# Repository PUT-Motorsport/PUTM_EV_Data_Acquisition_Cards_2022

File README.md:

# PUTM_EV_Data_Acquisition_Card_2022

## About the project
It's main task is to receive signals from sensors mounted on the car and analyze them and send to CAN-bus.

## Hardware design
The hardware part of the project is the PCB board which is connected to the sensors and CAN-bus. The microcontroller which is used is STM32L4P5RET6. The PCB is supply by 5VDC.

## Sensors
It receive signals from :   
 - ~~inductive sensors - there are used to measure wheels rotation speed~~
 - brake pressure sensors - which measure the pressure in the brake system
 - shutdown circuit sense:
1. BSPD
2. Overtravel switch
3. Driver's kill switch
4. Left and right kill switches
 - acceleration - from MPU on board

## Program flow diagram

)

## DMA and ADC timings consideration

The program is required to collect and relay data @ 100 ms.
Two adc peripherals are used to collect data from 3 analog sensors each.

* * *
ADC clock frequency: $32 MHz$

Sampling time: $92.5$ cycles - **reason:** High impedance inputs are used, subject to change

Oversampling: by 256

Sample conversion time: $T_{sample} + 12.5 = 105 cycles$

With oversampling: $T_{total} = 105 cycles * 256 samples = 26880 cycles$

$$
t = \frac{26800 * 3 channels}{32 * 10^6 Hz} = 2.52 * 10^{-3} s = 2.52 ms
$$

# 1D Kalman filter design for the IMU data

$$
\vec{x}(t + 1) = F(t + 1; t) * \vec{x}(t) + G * \vec{u} + w(t)
$$
$$
\vec{z} = H * \vec{x}(t)
$$

$$
\vec{x} = \begin{bmatrix} a_x \\ a_y \\ a_z \end{bmatrix}
$$

$$
F = \begin{bmatrix} 1 \\ 1 \\ 1 \end{bmatrix} \space\space\space H = \begin{bmatrix} 1 \\ 1 \\ 1 \end{bmatrix} \space\space\space G = [1] \space u = [0]
$$

$$
P(t + 1) = F(t)P(t) F(t)^T + Q(t)
$$

Since there is no way to calculate the change in acceleration, w(t) is estimated to gaussian N(0, $\sigma$) as process noise.

$$
Q(t) = \begin{bmatrix} \sigma_x \space 0 \space 0 \\ 0 \space \sigma_y \space 0 \\ 0 \space 0 \space \sigma_z\end{bmatrix}
$$

$$
\sigma_{process} = \sigma_x = \sigma_y = \sigma_z
$$

$$
R = \begin{bmatrix} ? ? ? \\ ? ? ? \\ ? ? ? \end{bmatrix}
$$

R to be selected.

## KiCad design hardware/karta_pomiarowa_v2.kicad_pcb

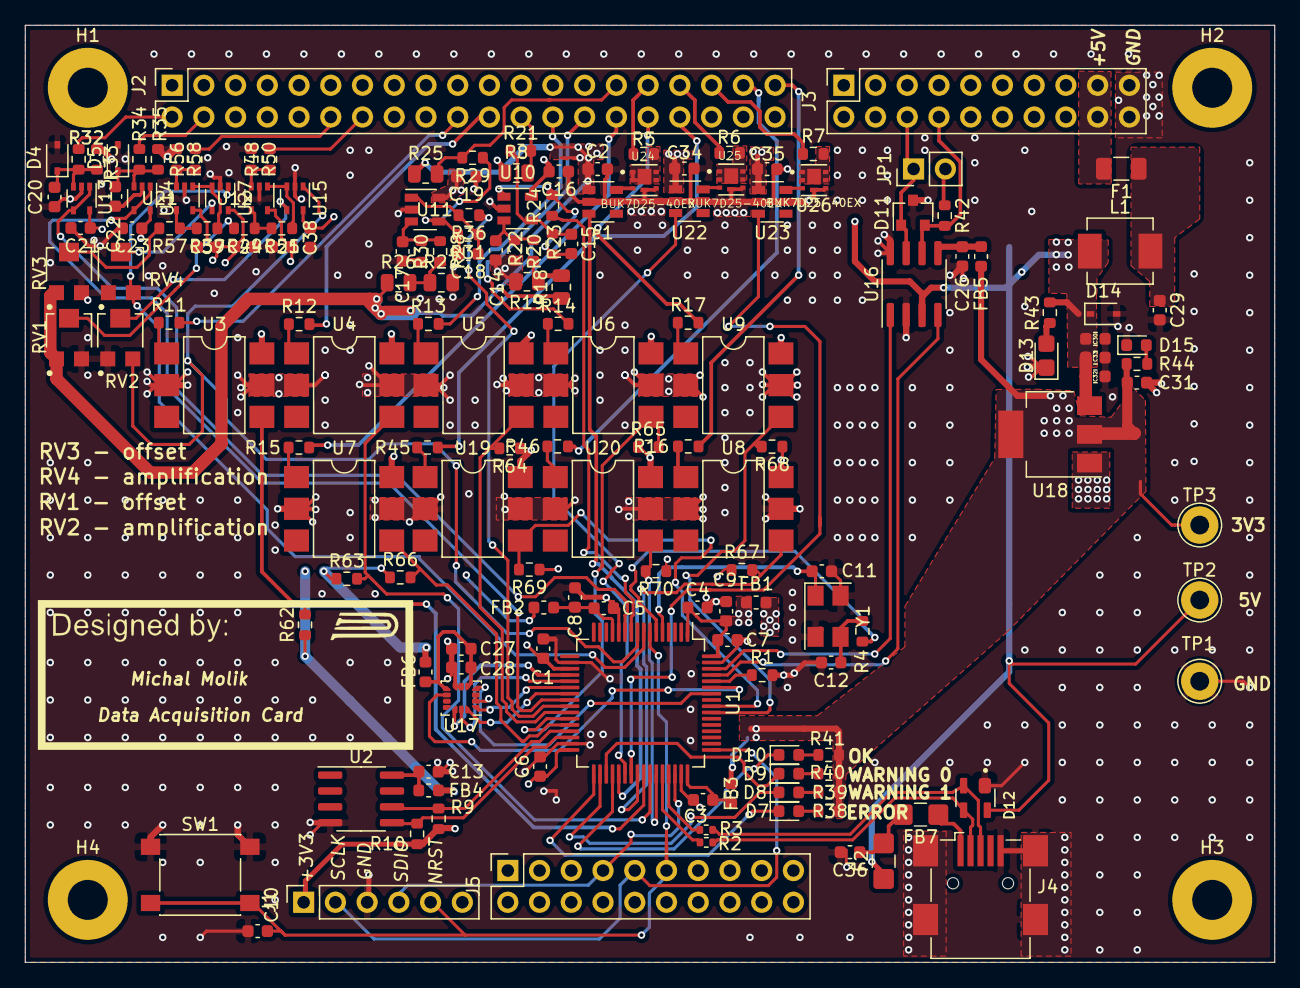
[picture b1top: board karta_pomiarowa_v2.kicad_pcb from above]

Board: 4 copper layers, 100.0 x 75.0 mm, 168 parts (0 on the bottom side), 118 nets.

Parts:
C1, C2, C3, C4, C5, C6, C7, C10, C13, C27, C28, C30, C31, C33, C34, C35, C36: 100nF; C_0603_1608Metric
C8: 1uF; C_0603_1608Metric
C9: 4.7uF; C_0603_1608Metric
C11, C12: 20p; C_0603_1608Metric
C14, C15, C17, C18: 1nF; C_0603_1608Metric
C16, C19, C20, C21, C22, C23, C24, C25, C26, C37, C38: 100n; C_0603_1608Metric
C29, C32: 10uF; C_0603_1608Metric
D4, D5: 6v5; D_SOD-323
D7, D8, D9, D10, D15: LED; LED_0603_1608Metric
D11: PESD2CAN.215; SOT-23
D12: PRTR5V0U2X; SOT190P230X110-4N
D13: LED; D_0805_2012Metric_Castellated
D14: 5.6v/6v; D_SOD-323
F1: 200mA; Fuse_1206_3216Metric
F2: 200mA; Fuse_1206_3216Metric_Castellated
FB1, FB2, FB3, FB4, FB5, FB6: 60R120MHz; L_0603_1608Metric
FB7: 1kOhm; Fuse_1206_3216Metric_Castellated
H1, H2, H3, H4: MountingHole; MountingHole_3.2mm_M3_Pad
J1: Conn_01x05_Male; PinSocket_1x06_P2.54mm_Vertical
J2: Conn_02x20_Odd_Even; PinSocket_2x20_P2.54mm_Vertical
J3, J5: Conn_02x10_Odd_Even; PinSocket_2x10_P2.54mm_Vertical
J4: USB_OTG; USB_Mini-B_Wuerth_65100516121_Horizontal
JP1: Jumper_NO_Small; PinHeader_1x02_P2.54mm_Vertical
L1: 6.8uH; L_Vishay_IHLP-2020
R1, R20, R21, R28, R29, R49, R57: 10k; R_0603_1608Metric
R2, R3: 22R; R_0402_1005Metric
R4, R42: R; R_0603_1608Metric
R5, R6, R7: 10R; R_0603_1608Metric
R8, R18, R19, R25, R26, R27: 5k; R_0805_2012Metric
R9, R10: 4.7k; R_0603_1608Metric
R11, R12, R13, R14, R15, R16, R17, R45, R46: 12k; R_0603_1608Metric
R22, R23, R30, R31, R51, R59: 47k; R_0603_1608Metric
R24, R36: 100R; R_0603_1608Metric
R32, R34, R48, R56, R62, R63, R64, R65, R66, R67, R68, R69, R70: 1k; R_0603_1608Metric
R33, R35, R38, R39, R40, R41, R44, R50, R58: 2k; R_0603_1608Metric
R43: 2.5k; R_0603_1608Metric
RV1, RV3: 2K; TRIM_TC33X-2-103E
RV2, RV4: 3K; TRIM_TC33X-2-103E
SW1: SW_MEC_5E; SW_Push_1P1T_NO_6x6mm_H9.5mm
TP1: GND; TestPoint_THTPad_D3.0mm_Drill1.5mm
TP2: 5V; TestPoint_THTPad_D3.0mm_Drill1.5mm
TP3: 3V3; TestPoint_THTPad_D3.0mm_Drill1.5mm
U1: STM32L4P5RET6; LQFP-64_10x10mm_P0.5mm
U2: M24C01-WMN; SOIC-8_3.9x4.9mm_P1.27mm
U3, U4, U5, U6, U7, U8, U9, U19, U20: H11L1; SMDIP-6_W7.62mm
U10, U11: TSX7191; SOT-23-5
U12, U13, U14, U15, U21, U27: MCP6001x-LT; SOT-353_SC-70-5
U16: ATA6561-GAQW-N; SOIC-8_3.9x4.9mm_P1.27mm
U17: IMS330DHCX; LGA-14_3x2.5mm_P0.5mm_LayoutBorder3x4y
U18: LM1117-3.3_copy; SOT-223
U22, U23: MCP14A0052T; SOT-23-6
U24, U25, U26: BUK7D25-40EX; TRANS_PMPB16EPX
Y1: 8MHz; Crystal_SMD_5032-4Pin_5.0x3.2mm
e1: MCP14A0052T; SOT-23-6

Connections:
+3V3: C16.2, C19.2, C21.2, C23.2, C24.2, C25.2, C31.1, C37.2, C38.2, FB1.1, FB2.1, FB3.1, FB4.1, FB5.1, FB6.1, J1.1, R9.1, R10.1, R38.1, R39.1, R40.1, R41.1, R44.1, R62.1, R63.1, R64.1, R65.1, R66.1, R67.1, R68.1, R69.1, R70.1, TP3.1, U3.6, U4.6, U5.6, U6.6, U7.6, U8.6, U9.6, U10.5, U11.5, U12.5, U13.5, U14.5, U15.5, U18.2, U18.4, U19.6, U20.6, U21.5, U27.5
+5V: C2.2, C30.1, C32.1, C33.1, C34.2, C35.2, D12.4, D14.1, F2.1, L1.1, R8.1, R18.1, R25.1, R26.1, R43.1, RV1.1, RV3.1, TP2.1, U16.3, U18.3, U22.1, U23.1, e1.1
+5VP: F1.2, J3.17, J3.18
/+uC: C1.1, C4.1, C6.1, C7.1, C9.1, FB1.2, U1.1, U1.19, U1.32, U1.64
/+uCa: C5.1, C8.1, FB2.2, U1.13
/+uCusb: C3.1, FB3.2, U1.48
/A0: RV4.3, U1.8, U27.1
/A1: RV2.3, U1.9, U15.1
/A2: R24.1, U1.10
/A3: U1.11, U13.1, U13.4
/A4: U1.24, U14.1, U14.4
/A5: R36.1, U1.25
/CAN_RX: U1.61, U16.4
/CAN_TRASCIVER/+3.3V_CAN: C26.1, FB5.2, U16.5
/CAN_TX: U1.62, U16.1
/DI0: R64.2, U1.26, U5.4
/DI1: R65.2, U1.27, U6.4
/DI2: R66.2, U1.28, U7.4
/DI3: R68.2, U1.55, U9.4
/DI4: R69.2, U1.56, U19.4
/DO0: U1.37, e1.3
/DO1: U1.38, U22.3
/DO2: U1.39, U23.3
/EEPROM/+3.3V_ee: C13.1, FB4.2, U2.8
/EEPROM_SCL: R9.2, U1.29, U2.6
/EEPROM_SDA: R10.2, U1.30, U2.5
/ISM330DHCXTR/+3.3V_IMS: C27.1, C28.1, FB6.2, U17.5, U17.8
/ISM_INT1: U1.58, U17.4
/ISM_INT2: U1.59, U17.9
/LED0: D7.1, U1.33
/LED1: D8.1, U1.34
/LED2: D9.1, U1.35
/LED3: D10.1, U1.36
/Left_s/IN+: R26.2, R27.1, R28.2
/OSC_IN: C11.2, U1.5, Y1.1
/OSC_OUT: R4.1, U1.6
/Right_s/IN+: R18.2, R19.1, R20.2
/SPI_CLK: U1.21, U17.13
/SPI_CS: U1.20, U17.12
/SPI_MISO: U1.22, U17.1
/SPI_MOSI: U1.23, U17.14
/TIM1_CH3: R70.2, U1.43, U20.4
/TIM3_CH4: R67.2, U1.40, U8.4
/WSS_TIM1_CH1: R62.2, U1.41, U3.4
/WSS_TIM1_CH2: R63.2, U1.42, U4.4
BRK_PRESS1: J2.12, R56.2
BRK_PRESS2: J2.14, R48.2
CANH: D11.1, J3.6, JP1.1, U16.7
CANL: D11.2, J3.8, R42.2, U16.6
GND: C1.2, C2.1, C3.2, C4.2, C5.2, C6.2, C7.2, C8.2, C9.2, C10.2, C11.1, C12.2, C13.2, C14.2, C16.1, C17.2, C19.1, C20.2, C21.1, C22.2, C23.1, C24.1, C25.1, C26.2, C27.2, C28.2, C29.2, C30.2, C31.2, C32.2, C33.2, C34.1, C35.1, C36.2, C37.1, C38.1, D4.2, D5.2, D11.3, D12.1, D13.1, D14.2, D15.1, J1.3, J3.19, J3.20, J4.5, J4.6, R1.2, R19.2, R22.2, R27.2, R30.2, R33.1, R35.1, R50.1, R58.1, RV1.3, RV2.1, RV3.3, RV4.1, SW1.1, TP1.1, U1.12, U1.18, U1.31, U1.47, U1.63, U2.4, U3.2, U3.5, U4.2, U4.5, U5.2, U5.5, U6.2, U6.5, U7.2, U7.5, U8.2, U8.5, U9.2, U9.5, U10.2, U11.2, U12.2, U13.2, U14.2, U15.2, U16.2, U16.8, U17.2, U17.3, U17.6, U17.7, U18.1, U19.2, U19.5, U20.2, U20.5, U21.2, U22.2, U22.5, U23.2, U23.5, U24.4, U24.8, U25.4, U25.8, U26.4, U26.8, U27.2, Y1.2, Y1.4, e1.2, e1.5
INERTIA: J2.32, R17.2
KILL_DRIVER: J2.26, R13.2
KILL_LEFT: J2.30, R15.2
KILL_RIGHT: J2.28, R14.2
NRST: C10.1, J1.5, J5.11, SW1.2, U1.7
unnamed: C12.1, R4.2, Y1.3
unnamed: C14.1, R20.1, R22.1, U10.3
unnamed: C15.1, R23.1, R24.2, U10.1
unnamed: C15.2, R21.1, R23.2, U10.4
unnamed: C17.1, R28.1, R30.1, U11.3
unnamed: C18.1, R31.1, R36.2, U11.1
unnamed: C18.2, R29.1, R31.2, U11.4
unnamed: C20.1, D4.1, R32.1, R33.2, U13.3
unnamed: C22.1, D5.1, R34.1, R35.2, U14.3
unnamed: C29.1, F1.1, L1.2
unnamed: C36.1, F2.2, FB7.2
unnamed: D7.2, R38.2
unnamed: D8.2, R39.2
unnamed: D9.2, R40.2
unnamed: D10.2, R41.2
unnamed: D13.2, R43.2
unnamed: D15.2, R44.2
unnamed: FB7.1, J4.1
unnamed: JP1.2, R42.1
unnamed: R1.1, U1.60
unnamed: R2.2, U1.44
unnamed: R3.2, U1.45
unnamed: R5.2, U24.1, U24.2, U24.5, U24.6, U24.7
unnamed: R6.2, U25.1, U25.2, U25.5, U25.6, U25.7
unnamed: R7.2, U26.1, U26.2, U26.5, U26.6, U26.7
unnamed: R11.1, U3.1
unnamed: R12.1, U4.1
unnamed: R13.1, U5.1
unnamed: R14.1, U6.1
unnamed: R15.1, U7.1
unnamed: R16.1, U8.1
unnamed: R17.1, U9.1
unnamed: R45.1, U19.1
unnamed: R46.1, U20.1
unnamed: R48.1, R50.2, U12.3
unnamed: R49.1, R51.2, U12.4
unnamed: R49.2, RV1.2
unnamed: R51.1, U12.1, U15.3
unnamed: R56.1, R58.2, U21.3
unnamed: R57.1, R59.2, U21.4
unnamed: R57.2, RV3.2
unnamed: R59.1, U21.1, U27.3
unnamed: RV2.2, U15.4
unnamed: RV4.2, U27.4
unnamed: U22.6, U25.3
unnamed: U23.6, U26.3
unnamed: U24.3, e1.6
OUTPUT0: J2.31, R5.1
OUTPUT1: J2.33, R6.1
OUTPUT2: J2.35, R7.1
OVERTRAVEL: J2.34, R45.2
PITOT1: J2.2, R32.2
PITOT2: J2.4, R34.2
SCLK: J1.2, J5.9, U1.49
SDIO: J1.4, J5.7, U1.46
SUSP_L: J2.29, R25.2, R29.2
SUSP_R: J2.24, R8.2, R21.2
TIM_IN0: J2.37, R46.2
TIM_IN1: J2.39, R16.2
USB+: D12.2, J4.3, R3.1
USB-: D12.3, J4.2, R2.1
WHSP1: J2.20, R11.2
WHSP2: J2.22, R12.2

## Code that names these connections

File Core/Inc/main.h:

/* USER CODE BEGIN Header */
/**
  ******************************************************************************
  * @file           : main.h
  * @brief          : Header for main.c file.
  *                   This file contains the common defines of the application.
  ******************************************************************************
  * @attention
  *
  * Copyright (c) 2022 STMicroelectronics.
  * All rights reserved.
  *
  * This software is licensed under terms that can be found in the LICENSE file
  * in the root directory of this software component.
  * If no LICENSE file comes with this software, it is provided AS-IS.
  *
  ******************************************************************************
  */
/* USER CODE END Header */

/* Define to prevent recursive inclusion -------------------------------------*/
#ifndef __MAIN_H
#define __MAIN_H

#ifdef __cplusplus
extern "C" {
#endif

/* Includes ------------------------------------------------------------------*/
#include "stm32l4xx_hal.h"

/* Private includes ----------------------------------------------------------*/
/* USER CODE BEGIN Includes */

/* USER CODE END Includes */

/* Exported types ------------------------------------------------------------*/
/* USER CODE BEGIN ET */

/* USER CODE END ET */

/* Exported constants --------------------------------------------------------*/
/* USER CODE BEGIN EC */

/* USER CODE END EC */

/* Exported macro ------------------------------------------------------------*/
/* USER CODE BEGIN EM */

/* USER CODE END EM */

/* Exported functions prototypes ---------------------------------------------*/
void Error_Handler(void);

/* USER CODE BEGIN EFP */

/* USER CODE END EFP */

/* Private defines -----------------------------------------------------------*/
#define ADC0_Pin GPIO_PIN_0
#define ADC0_GPIO_Port GPIOC
#define ADC1_Pin GPIO_PIN_1
#define ADC1_GPIO_Port GPIOC
#define ADC2_Pin GPIO_PIN_2
#define ADC2_GPIO_Port GPIOC
#define ADC3_Pin GPIO_PIN_3
#define ADC3_GPIO_Port GPIOC
#define SPI1_CS_Pin GPIO_PIN_4
#define SPI1_CS_GPIO_Port GPIOA
#define ADC4_Pin GPIO_PIN_4
#define ADC4_GPIO_Port GPIOC
#define ADC5_Pin GPIO_PIN_5
#define ADC5_GPIO_Port GPIOC
#define EEPROM_SCL_Pin GPIO_PIN_10
#define EEPROM_SCL_GPIO_Port GPIOB
#define EEPROM_SDA_Pin GPIO_PIN_11
#define EEPROM_SDA_GPIO_Port GPIOB
#define LED0_Pin GPIO_PIN_12
#define LED0_GPIO_Port GPIOB
#define LED1_Pin GPIO_PIN_13
#define LED1_GPIO_Port GPIOB
#define LED2_Pin GPIO_PIN_14
#define LED2_GPIO_Port GPIOB
#define LED3_Pin GPIO_PIN_15
#define LED3_GPIO_Port GPIOB
#define ISM_INT1_Pin GPIO_PIN_6
#define ISM_INT1_GPIO_Port GPIOB
void   MX_TIM3_Init(void);
/* USER CODE BEGIN Private defines */

/* USER CODE END Private defines */

#ifdef __cplusplus
}
#endif

#endif /* __MAIN_H */

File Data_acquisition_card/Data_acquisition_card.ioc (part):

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Mcu.Name=STM32L4P5R(G-E)Tx
Mcu.Package=LQFP64
Mcu.UserName=STM32L4P5RETx
PA10.GPIOParameters=GPIO_Label
PA10.GPIO_Label=RTD_input
PA10.Signal=GPXTI10
PA11.Mode=Device_Only
PA11.Signal=USB_OTG_FS_DM
PA12.Mode=Device_Only
PA12.Signal=USB_OTG_FS_DP
PA13\ (JTMS/SWDIO).Mode=Serial_Wire
PA13\ (JTMS/SWDIO).Signal=SYS_JTMS-SWDIO
PA14\ (JTCK/SWCLK).Mode=Serial_Wire
PA14\ (JTCK/SWCLK).Signal=SYS_JTCK-SWCLK
PA4.GPIOParameters=GPIO_Label
PA4.GPIO_Label=SPI1_CS
PA4.Signal=GPIO_Output
PA5.Mode=Full_Duplex_Master
PA5.Signal=SPI1_SCK
PA6.Mode=Full_Duplex_Master
PA6.Signal=SPI1_MISO
PA7.Mode=Full_Duplex_Master
PA7.Signal=SPI1_MOSI
PB0.GPIOParameters=GPIO_Label
PB0.GPIO_Label=Kill_driver_sense
PB0.Signal=GPIO_Input
PB1.GPIOParameters=GPIO_Label
PB1.GPIO_Label=Kill_right_sense
PB1.Signal=GPIO_Input
PB12.GPIOParameters=GPIO_Label
PB12.GPIO_Label=LED0
PB12.Signal=GPIO_Output
PB13.GPIOParameters=GPIO_Label
PB13.GPIO_Label=LED1
PB13.Signal=GPIO_Output
PB14.GPIOParameters=GPIO_Label
PB14.GPIO_Label=LED2
PB14.Signal=GPIO_Output
PB15.GPIOParameters=GPIO_Label
PB15.GPIO_Label=LED3
PB15.Signal=GPIO_Output
PB2.GPIOParameters=GPIO_Label
PB2.GPIO_Label=Kill_left_sense
PB2.Signal=GPIO_Input
PB3\ (JTDO/TRACESWO).GPIOParameters=GPIO_Label
PB3\ (JTDO/TRACESWO).GPIO_Label=BSPD_Sense
PB3\ (JTDO/TRACESWO).Signal=GPIO_Input
PB4\ (NJTRST).GPIOParameters=GPIO_Label
PB4\ (NJTRST).GPIO_Label=Overtravel_sense
PB4\ (NJTRST).Signal=GPIO_Output
PB8.Mode=CAN_Activate
PB8.Signal=CAN1_RX
PB9.Mode=CAN_Activate
PB9.Signal=CAN1_TX
PC0.GPIOParameters=GPIO_Label
PC0.GPIO_Label=ADC1_BRAKE_PRESSURE_1
PC0.Signal=ADCx_IN1
PC1.GPIOParameters=GPIO_Label
PC1.GPIO_Label=ADC1_BRAKE_PRESSURE_2
PC1.Signal=ADCx_IN2
PC2.GPIOParameters=GPIO_Label
PC2.GPIO_Label=ADC1_SUSP_R
PC2.Signal=ADCx_IN3
PC3.GPIOParameters=GPIO_Label
PC3.GPIO_Label=ADC2_ANALOG_1
PC3.Signal=ADCx_IN4
PC4.GPIOParameters=GPIO_Label
PC4.GPIO_Label=ADC2_ANALOG_2
PC4.Signal=ADCx_IN13
PC5.GPIOParameters=GPIO_Label
PC5.GPIO_Label=ADC2_SUSP_L
PC5.Signal=ADCx_IN14
PH0-OSC_IN\ (PH0).Mode=HSE-External-Oscillator
PH0-OSC_IN\ (PH0).Signal=RCC_OSC_IN
PH1-OSC_OUT\ (PH1).Mode=HSE-External-Oscillator
PH1-OSC_OUT\ (PH1).Signal=RCC_OSC_OUT
RCC.HSE_VALUE=8000000
RCC.SYSCLKFreq_VALUE=120000000
RCC.SYSCLKSource=RCC_SYSCLKSOURCE_PLLCLK
board=custom

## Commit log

2022-05-14 init
2022-05-19 ism manual
2022-05-19 ism run
2022-05-19 cleaning ism library
2022-05-21 added CAN library
2022-05-21 added ism_task wip
2022-05-22 added can_functions and meansure_task
2022-05-23 pheriperials fiies
2022-05-23 CAN transmit
2022-05-23 added adcc_data class
2022-05-24 fix can msg
2022-05-28 clear
2022-06-03 eeprom i2c work
2022-06-03 eeprom class
2022-06-17 update new lib
2022-06-21 fix pressure
2022-06-23 add startup
2022-06-26 Pre-VSV Fix
2022-07-20 Debounce fix to test
2022-07-21 working ts_button, CAN_LIBRARY updated
2022-07-30 Added rear brake pressure sensor readings
2022-08-24 Fixed symbolic links, updated project files
2022-09-15 Update gitignore
2022-09-15 Fixed and updated simulation files
2022-09-16 Cleanup
2022-09-16 Created IOC, wrote some code
2022-09-16 Re-added the CAN library
2022-09-16 Wrote CAN routines
2022-09-18 Wrote RTD and IMU code, minor fixes
2022-09-19 Minor fixed, verified code with CppCheck
2022-09-21 Fixed .gitignore, eliminated edgecases, fixed minor mistakes
2022-09-21 Added IMU as a submodule
2022-09-22 New IMU logic - works
2022-09-24 Minor fixes
2022-09-27 Added logic of averaging IMU readings
2022-10-02 New software (#2)
    * Cleanup
    * Created IOC, wrote some code
    * Re-added the CAN library
    * Wrote CAN routines
    * Wrote RTD and IMU code, minor fixes
    * Minor fixed, verified code with CppCheck
2022-10-02 Implemented and tested the Kalman filter
2022-10-03 Debugged the Kalman filter; fixed DMA issue
2022-10-04 Added USB VCP communication
2022-10-15 Added logging via the VCP
2022-10-21 Kalman (#3)
    * Implemented and tested the Kalman filter
    * Debugged the Kalman filter; fixed DMA issue
2022-10-21 Fixes
2022-10-21 Added brake pressure normalization
2022-10-25 Updated suspension potentiometers simulation
2022-10-25 Updated the schematic
2022-11-25 Virtual com port (#4)
    * Implemented and tested the Kalman filter
    * Debugged the Kalman filter; fixed DMA issue
    * Added USB VCP communication
    * Added logging via the VCP
    * Fixes
    * Added brake pressure normalization
